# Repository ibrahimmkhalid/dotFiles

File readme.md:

## My dot files

### Installer

Verified working on Ubuntu 24.04
Prepare for install:

```
sudo apt update -y && \
sudo apt install git ansible software-properties-common -y && \
git clone https://github.com/ibrahimmkhalid/dotFiles .dotFiles && \
cd .dotFiles
```

Do install (add required tags):

```
ansible-playbook local.yml --ask-become-pass --ask-vault-pass --skip-tags never --tags
```

Fix git remote after ssh keys installed

```
git remote remove origin && \
git remote add origin git@github.com:ibrahimmkhalid/dotFiles.git && \
git push --set-upstream origin main
```

List of availabe tags for ansible-playbook:

- meta tags
  - base
  - with-extra
  - with-gnome
  - clean (uninstall all the things)
  - never
  - always
- base tags (base)
  - git
  - nodejs (installs n package manager)
  - python (install uv package manager)
  - golang
  - nvim
  - scripts
  - ssh
  - tmux
  - zsh
- extra tags (with-extra)
  - lazygit
  - qmk
  - zathura
- gnome tags (with-gnome)
  - gnome-ext
  - gnome-settings
  - fonts

(There are many references to my username 'ibrahim'. If you are not me and want to use this repo, then make sure to go over all those changes)

## Credits

install-gnome-extensions script: https://github.com/ToasterUwU/install-gnome-extensions  
tmux-sessionizer script: https://github.com/ThePrimeagen/.dotfiles/blob/master/bin/.local/scripts/tmux-sessionizer  
qmk_firmware: https://github.com/qmk/qmk_firmware  
n (node version manager): https://github.com/tj/n
uv (python package manager): https://github.com/astral-sh/uv

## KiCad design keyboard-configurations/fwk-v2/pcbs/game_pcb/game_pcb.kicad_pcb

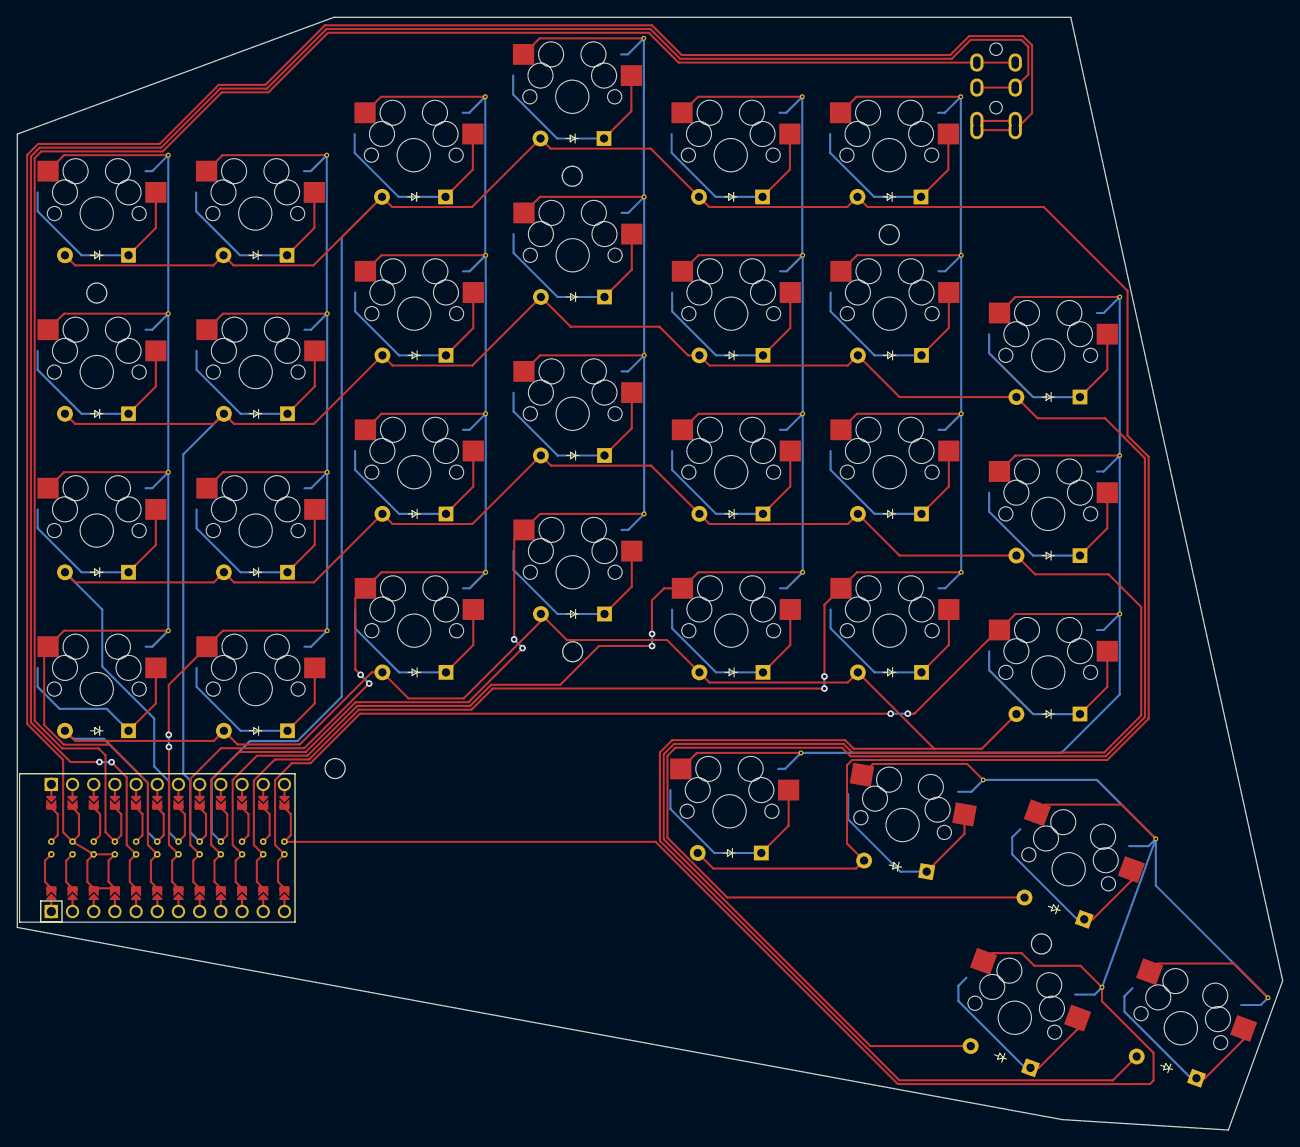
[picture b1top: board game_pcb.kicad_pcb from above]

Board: 2 copper layers, 151.7 x 133.4 mm, 66 parts (0 on the bottom side), 47 nets.

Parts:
D1, D2, D3, D4, D5, D6, D7, D8, D9, D10, D11, D12, D13, D14, D15, D16, D17, D18, D19, D20, D21, D22, D23, D24, D25, D26, D27, D28, D29, D30, D31, D32: ComboDiode
MCU1: ProMicro
S1, S2, S3, S4, S5, S6, S7, S8, S9, S10, S11, S12, S13, S14, S15, S16, S17, S18, S19, S20, S21, S22, S23, S24, S25, S26, S27, S28, S29, S30, S31, S32: MX
TRRS1: TRRS-PJ-320A-dual

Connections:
GND: MCU1.2, MCU1.21, MCU1.22, TRRS1.1, TRRS1.2
P2: MCU1.20, TRRS1.3
P3: MCU1.19, S24.2, S25.2, S26.2, S27.2
P4: MCU1.18, S1.2, S2.2, S3.2, S28.2
P5: MCU1.17, S4.2, S5.2, S6.2, S29.2
P6: MCU1.16, S7.2, S8.2, S9.2, S30.2
P7: MCU1.15, S10.2, S11.2, S12.2, S31.2
P8: MCU1.14, S13.2, S14.2, S15.2, S32.2
P9: MCU1.13, S16.2, S17.2, S18.2, S19.2
P10: MCU1.12, S20.2, S21.2, S22.2, S23.2
P15: D19.2, D20.2, D27.2, D28.2, D29.2, D30.2, D31.2, D32.2, MCU1.9
P18: D3.2, D6.2, D9.2, D12.2, D15.2, D18.2, D21.2, D26.2, MCU1.8
P19: D2.2, D5.2, D8.2, D11.2, D14.2, D17.2, D22.2, D25.2, MCU1.7
P20: D1.2, D4.2, D7.2, D10.2, D13.2, D16.2, D23.2, D24.2, MCU1.6
VCC: MCU1.4, TRRS1.4
extra_bottom: D16.1, S16.1
extra_home: D17.1, S17.1
extra_top: D18.1, S18.1
index_bottom: D10.1, S10.1
index_home: D11.1, S11.1
index_num: D31.1, S31.1
index_top: D12.1, S12.1
inner_bottom: D13.1, S13.1
inner_home: D14.1, S14.1
inner_num: D32.1, S32.1
inner_top: D15.1, S15.1
middle_bottom: D7.1, S7.1
middle_home: D8.1, S8.1
middle_num: D30.1, S30.1
middle_top: D9.1, S9.1
outer_bottom: D24.1, S24.1
outer_home: D25.1, S25.1
outer_num: D27.1, S27.1
outer_top: D26.1, S26.1
pinky_bottom: D1.1, S1.1
pinky_home: D2.1, S2.1
pinky_num: D28.1, S28.1
pinky_top: D3.1, S3.1
pos1_wextra: D19.1, S19.1
pos2_cluster: D20.1, S20.1
pos3_cluster: D21.1, S21.1
pos4_cluster: D22.1, S22.1
pos5_cluster: D23.1, S23.1
ring_bottom: D4.1, S4.1
ring_home: D5.1, S5.1
ring_num: D29.1, S29.1
ring_top: D6.1, S6.1

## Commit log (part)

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2023-06-30 update cursorline and set priority for color scheme
2023-06-30 remove print
2023-06-30 install zsh auto suggestions
2023-06-30 install undotree in nvim
2023-07-01 updates: added docker file for quick testing updated ergogen and qmk locations - removed tools from dotfiles updated ergogen and qmk build scripts updated install scripts
2023-07-01 udpate docker file and replace nvm with n
2023-07-02 fix tmux installation and fix user shell change
2023-07-02 update tmux conf
2023-07-02 update gnome installer
2023-07-02 udpate gnoem isntall scropt
2023-07-02 update install-shell script
2023-07-02 overhaul (#25)
    - Added dockerfile for testing dotfile changes
    - Updated gnome install script
    - Updated shell install script
    - install python
    - update zsh installer
    - replace nvm with n
2023-07-02 update nvim lazy
2023-07-02 remove unused stuff in nvim
2023-07-03 basic ansible with ssh
2023-07-03 make public
2023-07-03 install everything with ansible
2023-07-03 Make public (#27)
    * basic ansible with ssh
    * make public
    * install everything with ansible
    * rename ansible script
2023-07-03 remove traces of submodules
2023-07-04 remove icon madness
2023-07-04 single line install
2023-07-04 update dockerfile
2023-07-04 remove alacritty
2023-07-04 script no longer usable
2023-07-04 add gnome install script to ansible
2023-07-04 udpate zshrc
2023-07-05 rename ts to tmux-sessionizer
2023-07-05 update keyboard configurations in qmk
2023-07-06 fix ansible
2023-07-06 docker testing without pushing to github
2023-07-06 update git integration in neovim
2023-07-06 Revert "update git integration in neovim"
    This reverts commit f727286bc707057a7bf8ba9c94a9110b36ba2efc.
2023-07-06 Revert "Revert "update git integration in neovim""
    This reverts commit 609898611c2ae3c572498a5e338c567c9c37e890.
2023-07-06 update nvim git
2023-07-07 wsl rendering workaround
2023-07-07 add vb script for wsl workaround
2023-07-07 keep nordic theme
2023-07-07 everforest on gtk4 is incomplete, reverting to nordic
2023-07-07 ssh tag in ansible
2023-07-10 move zsh install from script to ansible
2023-07-10 update zsh ansible script
2023-07-10 update zsh yml
2023-07-10 update nvim keybinds
2023-07-10 update nvim lsp config
2023-07-12 add python configuration for nvim dap
2023-07-12 add rust configuration for nvim dap
2023-07-22 add fzf keybinds to zsh
2023-07-22 update lazyvim
2023-07-22 global todo script and tmux keybind
2023-07-22 update nvim
    contains breaking changes:
    - neogit
    - lazy.nvim
2023-07-23 Revert "update nvim"
    This reverts commit b49eacc9f3cc5e37c7ed009c7a218d4155c17cd6.
2023-07-26 tmux install ansible
2023-07-29 use default tmux window switch
2023-08-01 update tmux-sessionizer script
2023-08-01 update zshrc
2023-08-02 update cmp mappings to match vscode
2023-08-02 update how keymaps are set in nvim config
2023-08-03 simplify comment plugin for nvim
2023-08-03 restore cmp mappings with some improvements
2023-08-03 update keybinds in nvim
2023-08-06 extra nvim dap keymap because vscode
2023-08-15 organize better
2023-09-14 keyboard updates
2023-09-16 add keymap to emulate corne 3x5 layout
2023-09-17 update layout sheet for corne5x3
2023-09-17 add gaming layer to corne5x3
2023-12-08 major nvim update after long time
2023-12-09 remove old bad habit breaking changes use standard keybind for hover
2023-12-12 add custom snippets
    add python debug snippet
    remove default python debug config from dap.lua
2023-12-12 add confirmation prompt before closing dapui
    so that we can see the terminal output after the last line of execution
2023-12-12 add mklink script
    allows easliy creating symlink from windows to wsl
2023-12-16 add nvim to ansible
2023-12-16 update nvim script in ansible
2023-12-17 update docker file for ansible
2023-12-17 nvim add git conflict resolution
2023-12-17 update cmp keymaps
2023-12-17 add gh copilot to nvim
2023-12-17 add keybind to toggle or focus neotree
    honestly, i dont remember if this was how neotree worked before the
    start of this semester, but after having to use VSCode with the vim
    plugin, i got used to the way it worked there, and i wanted to make
    neotree work the same way. 🤷
2023-12-18 remove user input from dap end
2023-12-18 nvim: treesitter playground
    just for fun
2023-12-19 nvim: update lualine config
2023-12-19 nvim: update color scheme
    using everforest light hard
    installed many other color schemes
2023-12-19 tmux: updte tmux status colors to match nvim changes
    everforest, light, hard
2023-12-19 tmux: fix colors
2023-12-19 nvim: fix colorscheme loading
2023-12-19 nvim: update lazy packages to latest versions
2023-12-19 nvim: add filetypes to exclude from copilot
2023-12-20 nvim: global persistent copilot toggle
2023-12-20 nvim: replace reach with harpoon
2023-12-20 nvim: update neotree toggle behavior
2023-12-20 nvim: update harpoon descriptions
2023-12-20 nvim: separate dependencies and colorscheme
2023-12-20 nvim: only keep everforest colorsheme
2023-12-20 nvim: revert to older version of harpoon
    current version of harpoon breaks with nvim-cursorline plugin
2023-12-20 nvim: update lazy-lock.json
2023-12-20 wsl: add terminal settings files
2023-12-20 nvim: revert 2 commits
    fad1d53 'nvim: update lazy-lock.json'
    6ae6af1 'nvim: revert to older version of harpoon'
2023-12-20 nvim: update lazy packages
2023-12-21 nvim: use personal fork for nvim-cursorline
2023-12-21 nvim: add copilot indicator to lualine
2023-12-21 nvim: add more filetypes to be excluded from copilot
2023-12-21 nvim: update copilot keymaps
2023-12-22 nvim: udpate lualine
2023-12-22 major nvim update after long time (#29)
    - updated all packages to latest version
    - updated neovim to latest version
    - added keybind to remove "^M" after pasting from windows
    - separated common dependencies and colorschemes into their own files
    - updted colorscheme, matched it in tmux.conf
    - added github copilot
2023-12-22 nvim: update lazy
2023-12-22 scripts: redesign how the mklink script works
2023-12-23 nvim: add keymaps for prev and next in harpoon list
2023-12-24 refactor: moving keybaord configs to own repo
2023-12-26 update: add git configs to ansible script
2023-12-26 ansible: add some base tasks
2023-12-26 ansible: add lazygit install to ansible task
2023-12-26 refactor(ansible): move base tasks to local yml
2023-12-26 refactor(ansible): de-indent includes in local.yml
2023-12-26 fix(nvim/copilot): actually turn off copilot on startup
2023-12-27 feat(ansible): better tag management
2023-12-27 feat(ansible): move more install script instructions to ansible
2023-12-27 feat(ansible): more more install script instructions to ansible
2023-12-27 fix(ansible): use stable nvim version for install
2023-12-27 chore(nvim/bufferline): move all relevant options for specific plugin to that plugin's config file
2023-12-28 chore(nvim): update lazy-lock.json
2023-12-28 feat(nvim): remove nvim-ufo
2023-12-28 revert c2b772d 'feat(nvim): remove nvim-ufo'
2023-12-28 feat(nvim/nvim-ufo): update to better ufo config
2023-12-28 chore(ansible): move lazygit taks to apps dir
2023-12-28 feat(ansible): add ergogen to ansible script
2023-12-28 feat(ansible): add qmk to ansible script
2023-12-28 feat(ansible): convert all of install-shell.sh to ansible
2023-12-28 fix(ansible/zsh): make repeatable
2023-12-30 feat(ansible): add uninstall scripts
2023-12-30 refactor(ansible): better tag management
2023-12-31 refactor(ansible): better task names
2023-12-31 fix ansible qmk
2023-12-31 update(ansible): remove unused script
2024-01-01 update(gnome): update colors to match everforest light hard
2024-01-01 feat(ansible/gnome): overhaul ansible script to set gnome
2024-01-01 fix(ansible/nvim): remove all dirs when uninstalling nvim
2024-01-02 fix package name
2024-01-02 fix: missing colon
2024-01-03 update wallpaper
2024-01-03 feat(ansible/system): migrate to fedora?
2024-01-03 fix(ansible): add local dirs always
2024-01-04 update gnome dconf
2024-01-04 update gnome terminal settings
2024-01-05 update dash to dock settings
2024-01-05 refactor(nvim/harpoon): blazingly fast keymaps
2024-01-05 refactor(nvim/harpoon): better keymaps without conflicts
2024-01-05 feat(nvim+zshrc): source project env file if exists create snippets for basic python project env file on wayland
2024-01-05 udpate lazy nvim
2024-01-05 fix(nvim/markdown-preview): Lazy updates would break for this plugin
2024-01-05 Revert "update"
    This reverts commit fab4e9db00e91673776639110c25012eaf0abdcf.
2024-01-08 chore(nvim/snippets): add python proj snippet
2024-01-10 feat(nvim): replace jedi lsp with pyright lsp
2024-01-10 chore(nvim/lazy): update lazy-lock.json
2024-01-20 feat(dev tools): install turso db cli
    ansible script for turso untested
2024-01-20 feat(dev tools): go lang installer script in ansible
2024-01-26 udpate tmux keybinds
2024-01-26 update nvim lazy-lock
2024-02-04 update tmux sessionizer script
2024-02-05 add dark mode toggle to guillotine
2024-02-05 feat(colormode): added script for gnome stuff added placeholder for wsl
2024-02-05 feat(colormode): added tmux config
2024-02-05 remove empty lien
2024-02-05 feat(colormode): added nvim cofnig
2024-02-05 only run tmux source if tmux is running
2024-02-05 feat(colormode): add zsh/tmux bindings for dark mode toggle
2024-02-06 fix(colormode): gnome user theme fix
2024-02-06 feat(colormode): toggle working on windows terminal
2024-02-06 udpate windows terminal config
2024-02-08 convert gnome terminal color from rgb() to hexcodes
2024-02-08 only edit gnome terminal colors on toggle-dark-mode
2024-02-08 feat(colormode): vscode added
2024-02-10 remove ergogen from ansible installer
2024-02-10 add zathura and latex support
2024-02-11 wsl compatibility for vimtex
2024-02-11 refactor tmux-sessionizer script
2024-02-11 add uni courses
2024-02-12 update toggle-dark-mode script
2024-02-12 use better wsl detection
2024-02-12 bash is hard :(
2024-02-13 remove tmux-session script
2024-02-15 update script
2024-02-16 open zathura maximized always
2024-02-19 update jupyter ascending stuff
2024-02-20 update nvim keymaps for jupyter
2024-02-21 udpte study-something script
2024-02-23 turns out i was not following symlinks.... oops
2024-02-24 update tmux-sessionizer
2024-03-04 update jupyter keybinds
2024-03-04 update(nvim/keybinds): create keybind to reformat written paragraph
2024-03-04 feat(nvim/mason): add formatter support
2024-03-04 feat(nvim/mason): ensure_installed for anything
2024-04-24 nvim: update keybind
2024-04-24 nvim: add quick navigation to quick fix list
2024-05-27 nvim: improve tab navigation, disable toggle terminal
2024-06-11 nvim: update lazy lock
2024-06-11 nvim: update harpoon
2024-06-17 update go package in ansible installer
2024-06-20 nvim: clean up configs
2024-06-20 nvim: update
2024-06-25 update mason
2024-06-25 nvim: keymap for conform
2024-06-25 nvim: remove copilot
2024-08-13 add keybind
2024-09-24 nvim:jupyter: execute and new cell
2024-09-24 nvim:cmp: remove custom tab
2024-09-28 add snippet for python
2024-09-28 nvim:snippets: autoformat
2024-12-30 reformat
2024-12-30 add more keymaps
2025-01-26 update courses
2025-02-01 update windows terminal config
2025-02-03 add llm to terminal workflow
2025-04-20 nvim: update python formatter
2025-04-27 update diskUse script
2025-05-14 remove turso
2025-05-14 add python uv
2025-05-14 add uv stuff
2025-05-14 update ansible tasks
2025-05-16 remove sjsu stuff from scripts and others
2025-06-03 update tmux sessionizer
2025-06-10 remove automatic tmux hydration
2025-07-25 update ansible scripts
2025-07-25 add todo file
2025-07-25 install python when installing qmk
2025-07-25 ansible: install extensions gnome shell
2025-08-17 nvim: adding windsurf
2025-09-24 make zshrc system agnostic
2025-09-24 add ghostty config
2025-09-25 make global todo script agnostic
2025-10-01 add .DS_Store to gitignore
2025-10-02 update ghostty config
2025-12-28 reorg
2026-02-14 add dev start script
2026-02-14 update dev start script
2026-04-20 update askllm script
2026-04-21 oops
2026-05-17 update nvim configs (v0.12)
2026-05-18 update nvim
2026-05-21 update colorscheme stuff
2026-05-22 add swiftbar toggle for dark mode
2026-05-22 fix colorscheme toggle signla options
